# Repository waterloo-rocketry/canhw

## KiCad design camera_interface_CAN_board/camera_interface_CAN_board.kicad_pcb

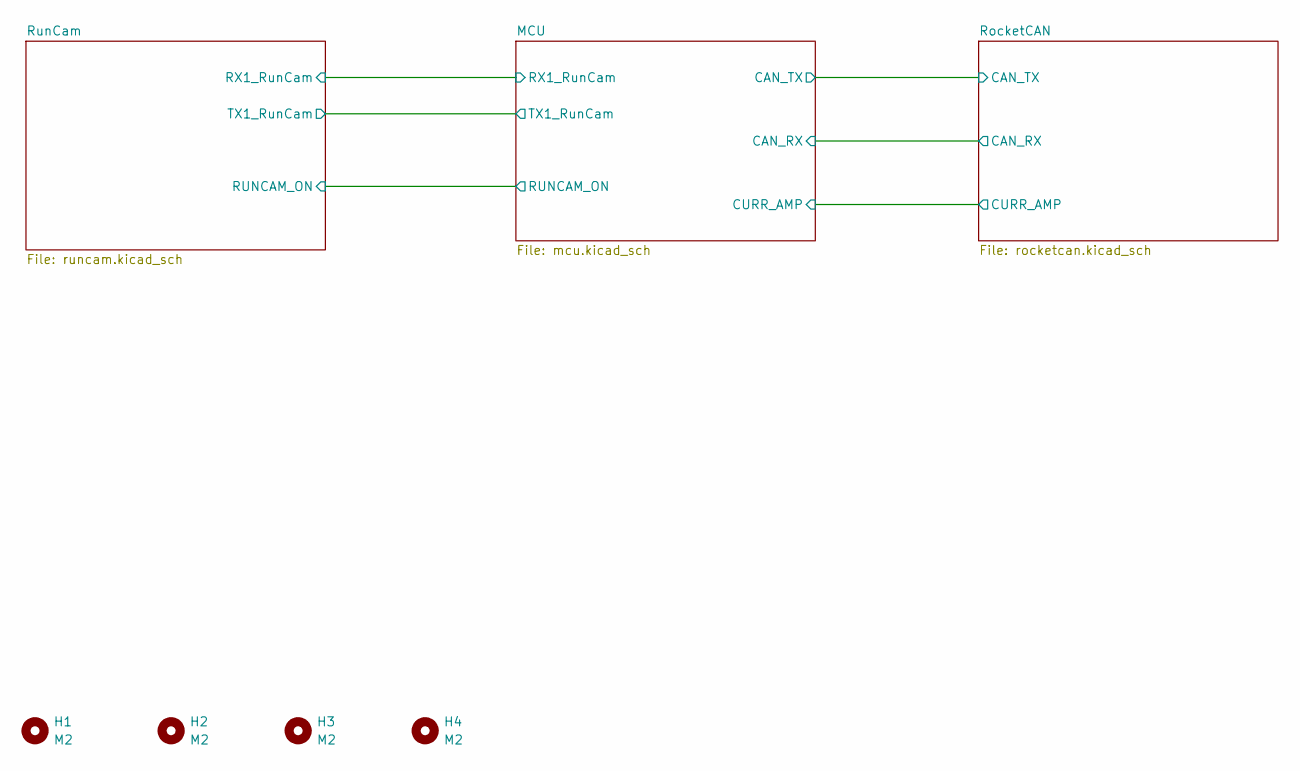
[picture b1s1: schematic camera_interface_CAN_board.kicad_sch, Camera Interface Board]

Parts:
H1, H2, H3, H4: M2; MountingHole_2.2mm_M2

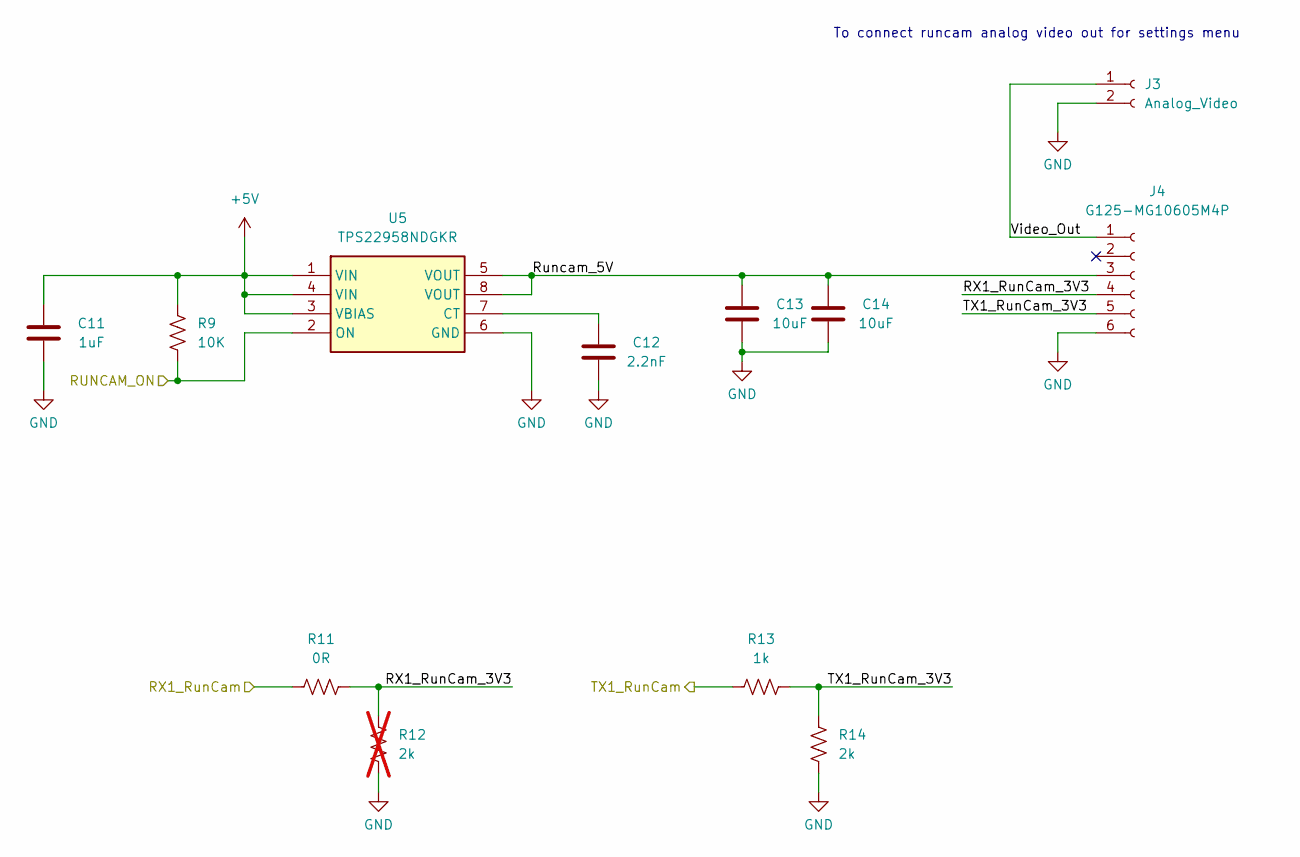
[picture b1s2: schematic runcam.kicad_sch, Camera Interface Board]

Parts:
C11: 1uF; C_0603_1608Metric_Pad1.08x0.95mm_HandSolder
C12: 2.2nF; C_0603_1608Metric_Pad1.08x0.95mm_HandSolder
C13, C14: 10uF; C_0805_2012Metric_Pad1.18x1.45mm_HandSolder
J3: Analog_Video; PinSocket_1x02_P1.27mm_Vertical
J4: G125-MG10605M4P; connector_Harwin_G125–MG10605M4P
R9: 10K; R_0603_1608Metric_Pad0.98x0.95mm_HandSolder
R11: 0R; R_0603_1608Metric_Pad0.98x0.95mm_HandSolder
R12: 2k; R_0603_1608Metric_Pad0.98x0.95mm_HandSolder; not fitted
R13: 1k; R_0603_1608Metric_Pad0.98x0.95mm_HandSolder
R14: 2k; R_0603_1608Metric_Pad0.98x0.95mm_HandSolder
U5: TPS22958NDGKR; SOP65P490X110-8N; Manufacturer_Part_Number TPS22958NDGKR

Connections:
+5V: C11.2, R9.1, U5.1 (VIN), U5.3 (VBIAS), U5.4 (VIN); also elsewhere on the board
/MCU/RUNCAM_ON: R9.2, U5.2 (ON); also elsewhere on the board
/MCU/RX1_RunCam: R11.1; also elsewhere on the board
/MCU/TX1_RunCam: R13.1; also elsewhere on the board
/RunCam/RX1_RunCam_3V3: J4.4, R11.2, R12.2
/RunCam/Runcam_5V: C13.2, C14.2, J4.3, U5.5 (VOUT), U5.8 (VOUT)
/RunCam/TX1_RunCam_3V3: J4.5, R13.2, R14.2
/RunCam/Video_Out: J3.1, J4.1
GND: C11.1, C12.1, C13.1, C14.1, J3.2, J4.6, R12.1, R14.1, U5.6 (GND); also elsewhere on the board
unnamed: C12.2, U5.7 (CT)

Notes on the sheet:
To connect runcam analog video out for settings menu

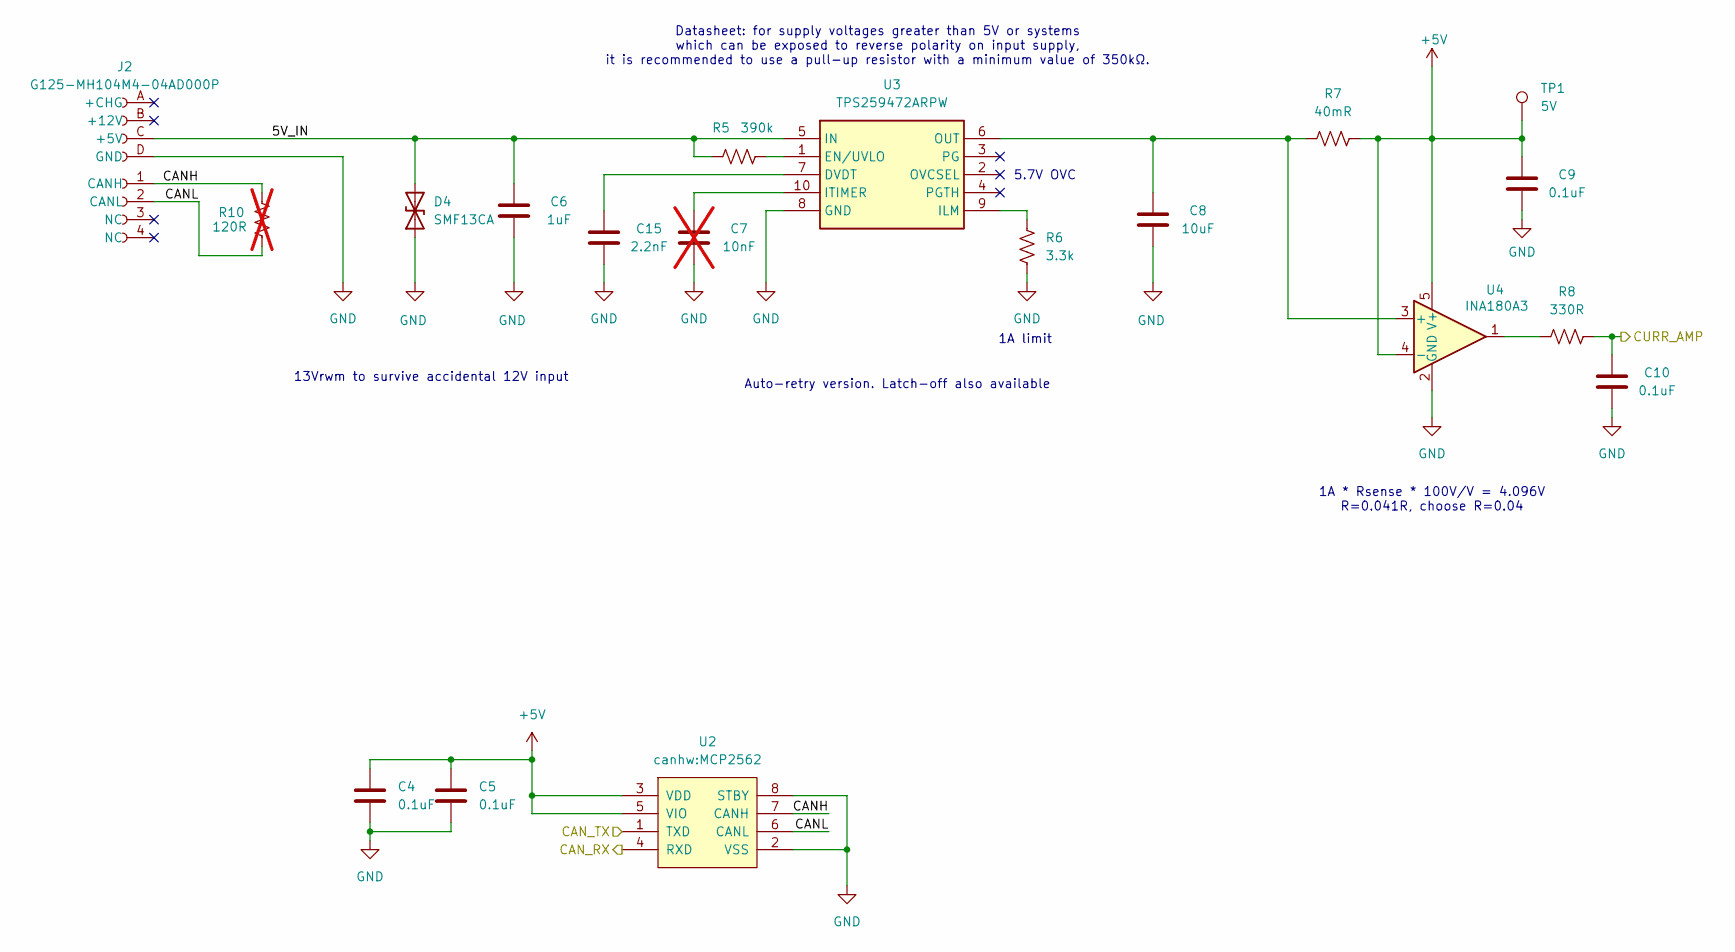
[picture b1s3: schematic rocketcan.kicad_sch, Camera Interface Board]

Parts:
C4, C5, C9, C10: 0.1uF; C_0603_1608Metric_Pad1.08x0.95mm_HandSolder
C6: 1uF; C_0603_1608Metric_Pad1.08x0.95mm_HandSolder
C7: 10nF; C_0603_1608Metric_Pad1.08x0.95mm_HandSolder; not fitted
C8: 10uF; C_0805_2012Metric_Pad1.18x1.45mm_HandSolder
C15: 2.2nF; C_0603_1608Metric_Pad1.08x0.95mm_HandSolder
D4: SMF13CA; D_SMF
J2: G125-MH104M4-04AD000P; connector_Harwin_G125-MH104M4-04AD000P
R5: 390k; R_0603_1608Metric_Pad0.98x0.95mm_HandSolder
R6: 3.3k; R_0603_1608Metric_Pad0.98x0.95mm_HandSolder
R7: 40mR; R_0805_2012Metric_Pad1.20x1.40mm_HandSolder
R8: 330R; R_0603_1608Metric_Pad0.98x0.95mm_HandSolder
R10: 120R; R_0603_1608Metric_Pad0.98x0.95mm_HandSolder; not fitted
TP1: 5V; TestPoint_Pad_D1.0mm
U2: canhw:MCP2562; SOIC-8_3.9x4.9mm_P1.27mm
U3: TPS259472ARPW; TPS25947xx
U4: INA180A3; SOT-23-5_HandSoldering

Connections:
+5V: C4.1, C5.1, C9.2, R7.1, TP1.1 (1_1), U2.3 (VDD), U2.5 (VIO), U4.4 (-), U4.5 (V+); also elsewhere on the board
/MCU/CAN_RX: U2.4 (RXD); also elsewhere on the board
/MCU/CAN_TX: U2.1 (TXD); also elsewhere on the board
/MCU/CURR_AMP: C10.2, R8.1; also elsewhere on the board
/RocketCAN/5V_IN: C6.2, D4.2 (A2), J2.C (+5V), R5.1, U3.5 (IN)
/RocketCAN/CANH: J2.1 (CANH), R10.2, U2.7 (CANH)
/RocketCAN/CANL: J2.2 (CANL), R10.1, U2.6 (CANL)
GND: C4.2, C5.2, C6.1, C7.1, C8.1, C9.1, C10.1, C15.1, D4.1 (A1), J2.D (GND), R6.2, U2.2 (VSS), U2.8 (STBY), U3.8 (GND), U4.2 (GND); also elsewhere on the board
unnamed: R8.2, U4.1
unnamed: C15.2, U3.7 (DVDT)
unnamed: R5.2, U3.1 (EN/UVLO)
unnamed: R6.1, U3.9 (ILM)
unnamed: C7.2, U3.10 (ITIMER)
unnamed: C8.2, R7.2, U3.6 (OUT), U4.3 (+)

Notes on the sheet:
13Vrwm to survive accidental 12V input
Auto-retry version. Latch-off also available
5.7V OVC
Datasheet: for supply voltages greater than 5V or systems which can be exposed to reverse polarity on input supply, it is recommended to use a pull-up resistor with a minimum value of 350kΩ.
1A limit
1A * Rsense * 100V/V = 4.096V R=0.041R, choose R=0.04

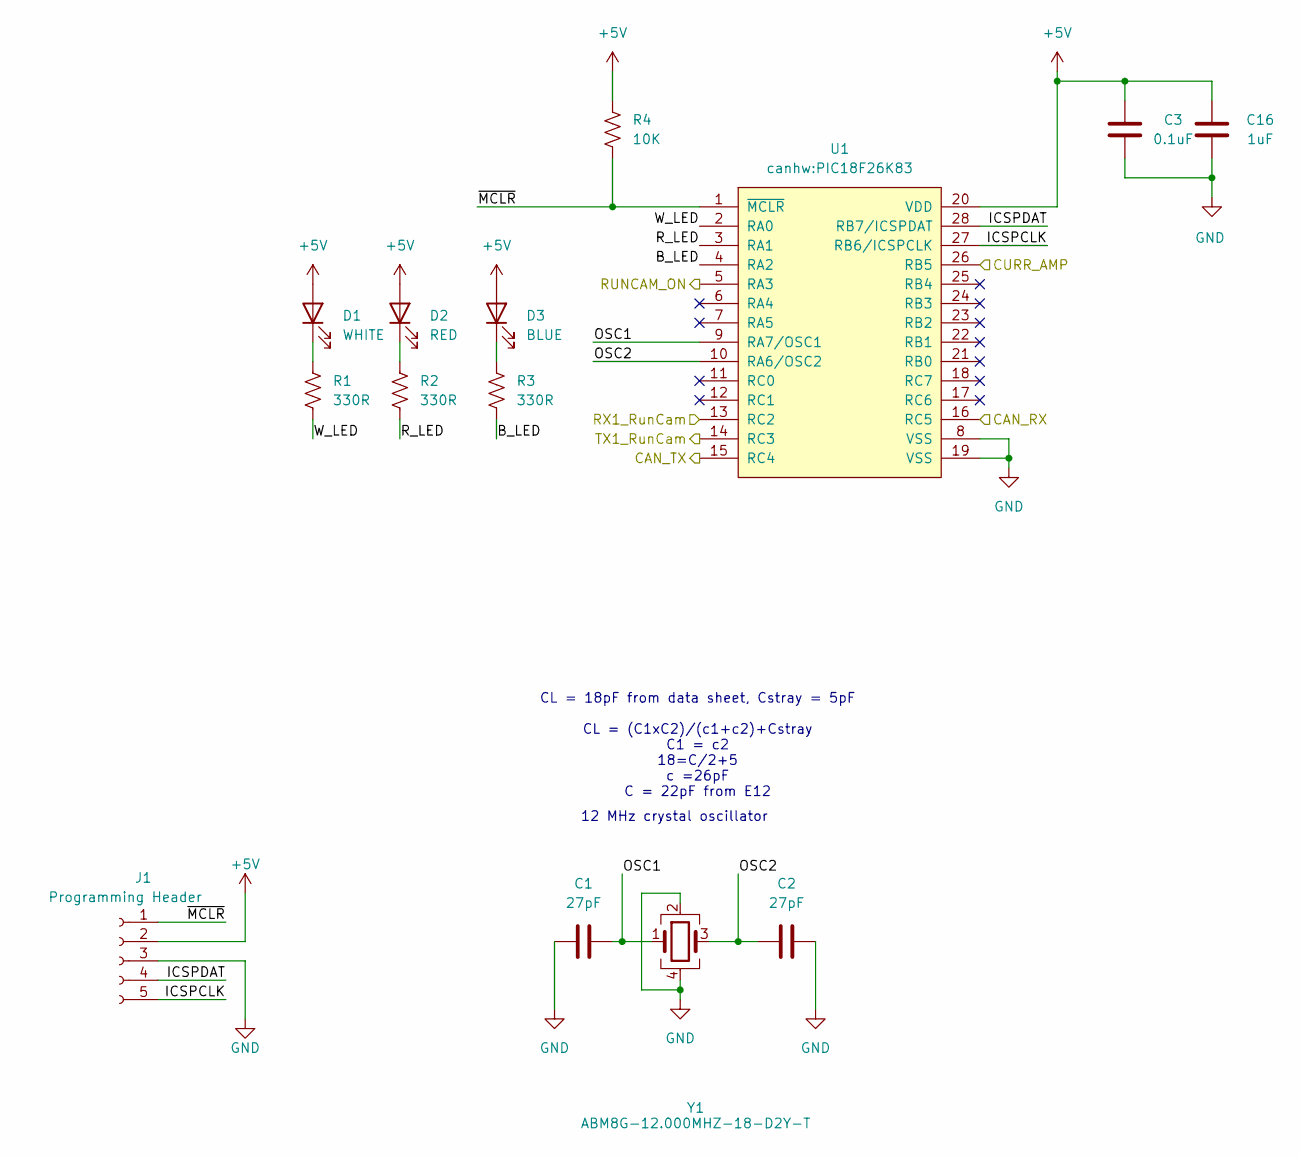
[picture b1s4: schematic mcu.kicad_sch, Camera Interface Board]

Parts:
C1, C2: 27pF; C_0603_1608Metric_Pad1.08x0.95mm_HandSolder
C3: 0.1uF; C_0603_1608Metric_Pad1.08x0.95mm_HandSolder
C16: 1uF; C_0603_1608Metric_Pad1.08x0.95mm_HandSolder
D1: WHITE; LED_1206_3216Metric
D2: RED; LED_1206_3216Metric
D3: BLUE; LED_1206_3216Metric
J1: Programming Header; PinSocket_5x2.54_SMD_90deg_952-3198-1-ND
R1, R2, R3: 330R; R_0603_1608Metric_Pad0.98x0.95mm_HandSolder
R4: 10K; R_0603_1608Metric_Pad0.98x0.95mm_HandSolder
U1: canhw:PIC18F26K83; SOIC-28W_7.5x18.7mm_P1.27mm
Y1: ABM8G-12.000MHZ-18-D2Y-T; Crystal_SMD_Abracon_ABM8G-4Pin_3.2x2.5mm

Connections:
+5V: C3.2, C16.2, D1.2 (A), D2.2 (A), D3.2 (A), J1.2, R4.1, U1.20 (VDD); also elsewhere on the board
/MCU/B_LED: R3.2, U1.4 (RA2)
/MCU/CAN_RX: U1.16 (RC5); also elsewhere on the board
/MCU/CAN_TX: U1.15 (RC4); also elsewhere on the board
/MCU/CURR_AMP: U1.26 (RB5); also elsewhere on the board
/MCU/ICSPCLK: J1.5, U1.27 (RB6/ICSPCLK)
/MCU/ICSPDAT: J1.4, U1.28 (RB7/ICSPDAT)
/MCU/OSC1: C1.1, U1.9 (RA7/OSC1), Y1.1
/MCU/OSC2: C2.2, U1.10 (RA6/OSC2), Y1.3
/MCU/RUNCAM_ON: U1.5 (RA3); also elsewhere on the board
/MCU/RX1_RunCam: U1.13 (RC2); also elsewhere on the board
/MCU/R_LED: R2.2, U1.3 (RA1)
/MCU/TX1_RunCam: U1.14 (RC3); also elsewhere on the board
/MCU/W_LED: R1.2, U1.2 (RA0)
/MCU/~MCLR: J1.1, R4.2, U1.1 (~MCLR)
GND: C1.2, C2.1, C3.1, C16.1, J1.3, U1.8 (VSS), U1.19 (VSS), Y1.2, Y1.4; also elsewhere on the board
unnamed: D1.1 (K), R1.1
unnamed: D2.1 (K), R2.1
unnamed: D3.1 (K), R3.1

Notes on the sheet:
12 MHz crystal oscillator
CL = 18pF from data sheet, Cstray = 5pF CL = (C1xC2)/(c1+c2)+Cstray C1 = c2 18=C​/2+5 c =26pF C = 22pF from E12​

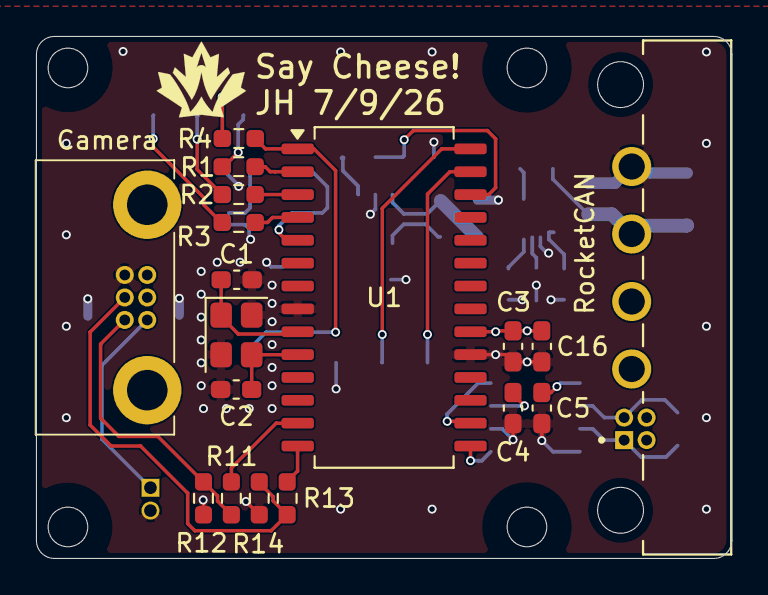
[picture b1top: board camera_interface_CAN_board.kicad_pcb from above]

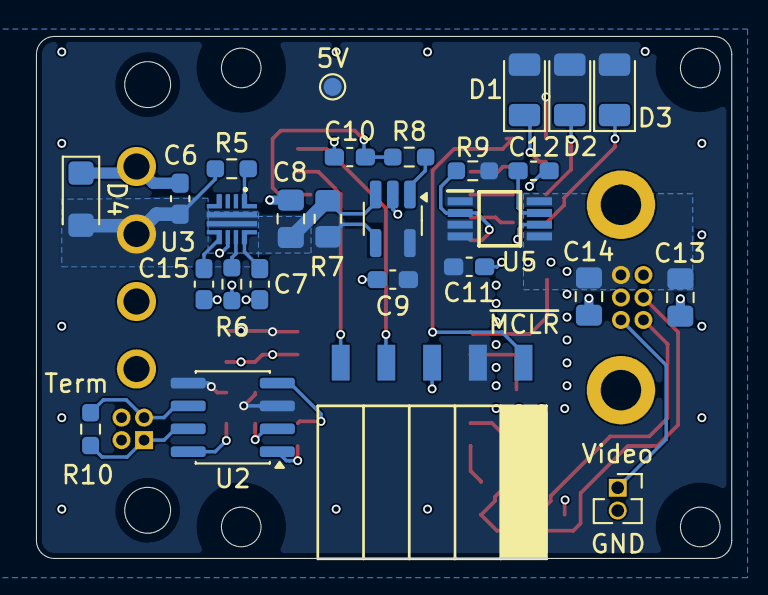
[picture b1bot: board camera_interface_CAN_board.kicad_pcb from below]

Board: 4 copper layers, 38.6 x 29.0 mm, 49 parts (27 on the bottom side), 33 nets.

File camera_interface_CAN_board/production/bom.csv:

Designator,Footprint,Quantity,Value,LCSC Part #
"C1, C2",0603,2,27pF,
"C10, C3, C4, C5, C9",0603,5,0.1uF,
"C11, C16, C6",0603,3,1uF,
"C12, C15",0603,2,2.2nF,
"C13, C14, C8",0805,3,10uF,
C7,0603,1,10nF,
D1,1206,1,WHITE,
D2,1206,1,RED,
D3,1206,1,BLUE,
D4,D_SMF,1,SMF13CA,
J1,PinSocket_5x2.54_SMD_90deg_952-3198-1-ND,1,Programming Header,
J2,connector_Harwin_G125-MH104M4-04AD000P,1,G125-MH104M4-04AD000P,
J3,PinSocket_1x02_P1.27mm_Vertical,1,Analog_Video,
J4,connector_Harwin_G125–MG10605M4P,1,G125-MG10605M4P,
"R1, R2, R3, R8",0603,4,330R,
R10,0603,1,120R,
R11,0603,1,0R,
"R12, R14",0603,2,2k,
R13,0603,1,1k,
"R4, R9",0603,2,10K,
R5,0603,1,390k,
R6,0603,1,3.3k,
R7,0805,1,40mR,
TP1,TestPoint_Pad_D1.0mm,1,5V,
U1,SOIC-28W_7.5x18.7mm_P1.27mm,1,canhw:PIC18F26K83,
U2,SOIC-8_3.9x4.9mm_P1.27mm,1,canhw:MCP2562,
U3,TPS25947xx,1,TPS259472ARPW,
U4,SOT-23-5_HandSoldering,1,INA180A3,
U5,SOP65P490X110-8N,1,TPS22958NDGKR,
Y1,Crystal_SMD_Abracon_ABM8G-4Pin_3.2x2.5mm,1,ABM8G-12.000MHZ-18-D2Y-T,

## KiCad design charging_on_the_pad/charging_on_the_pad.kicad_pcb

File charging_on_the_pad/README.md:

# Charging On the Pad 
A charger board on the CAN bus that includes the battery, charging port connection, and additional power connections to live telemetry transmitter.
Clickup: https://app.clickup.com/8608989/v/li/176275976
Drive: https://drive.google.com/drive/folders/1WU_OsI1vf2b53sMAvz4AfjsN1jmYpsuN?usp=sharing

The system must provide CAN communication to the rocket from the ground side as long as the rocket is on the pad
The system should report the charge status, battery voltage, and current to CAN bus
The system should be able to turn off or on the CAN bus power. LTT should be kept 
The connector must be strong enough to stay in by itself, but weak enough to be pulled off by the rocket without affecting the launch

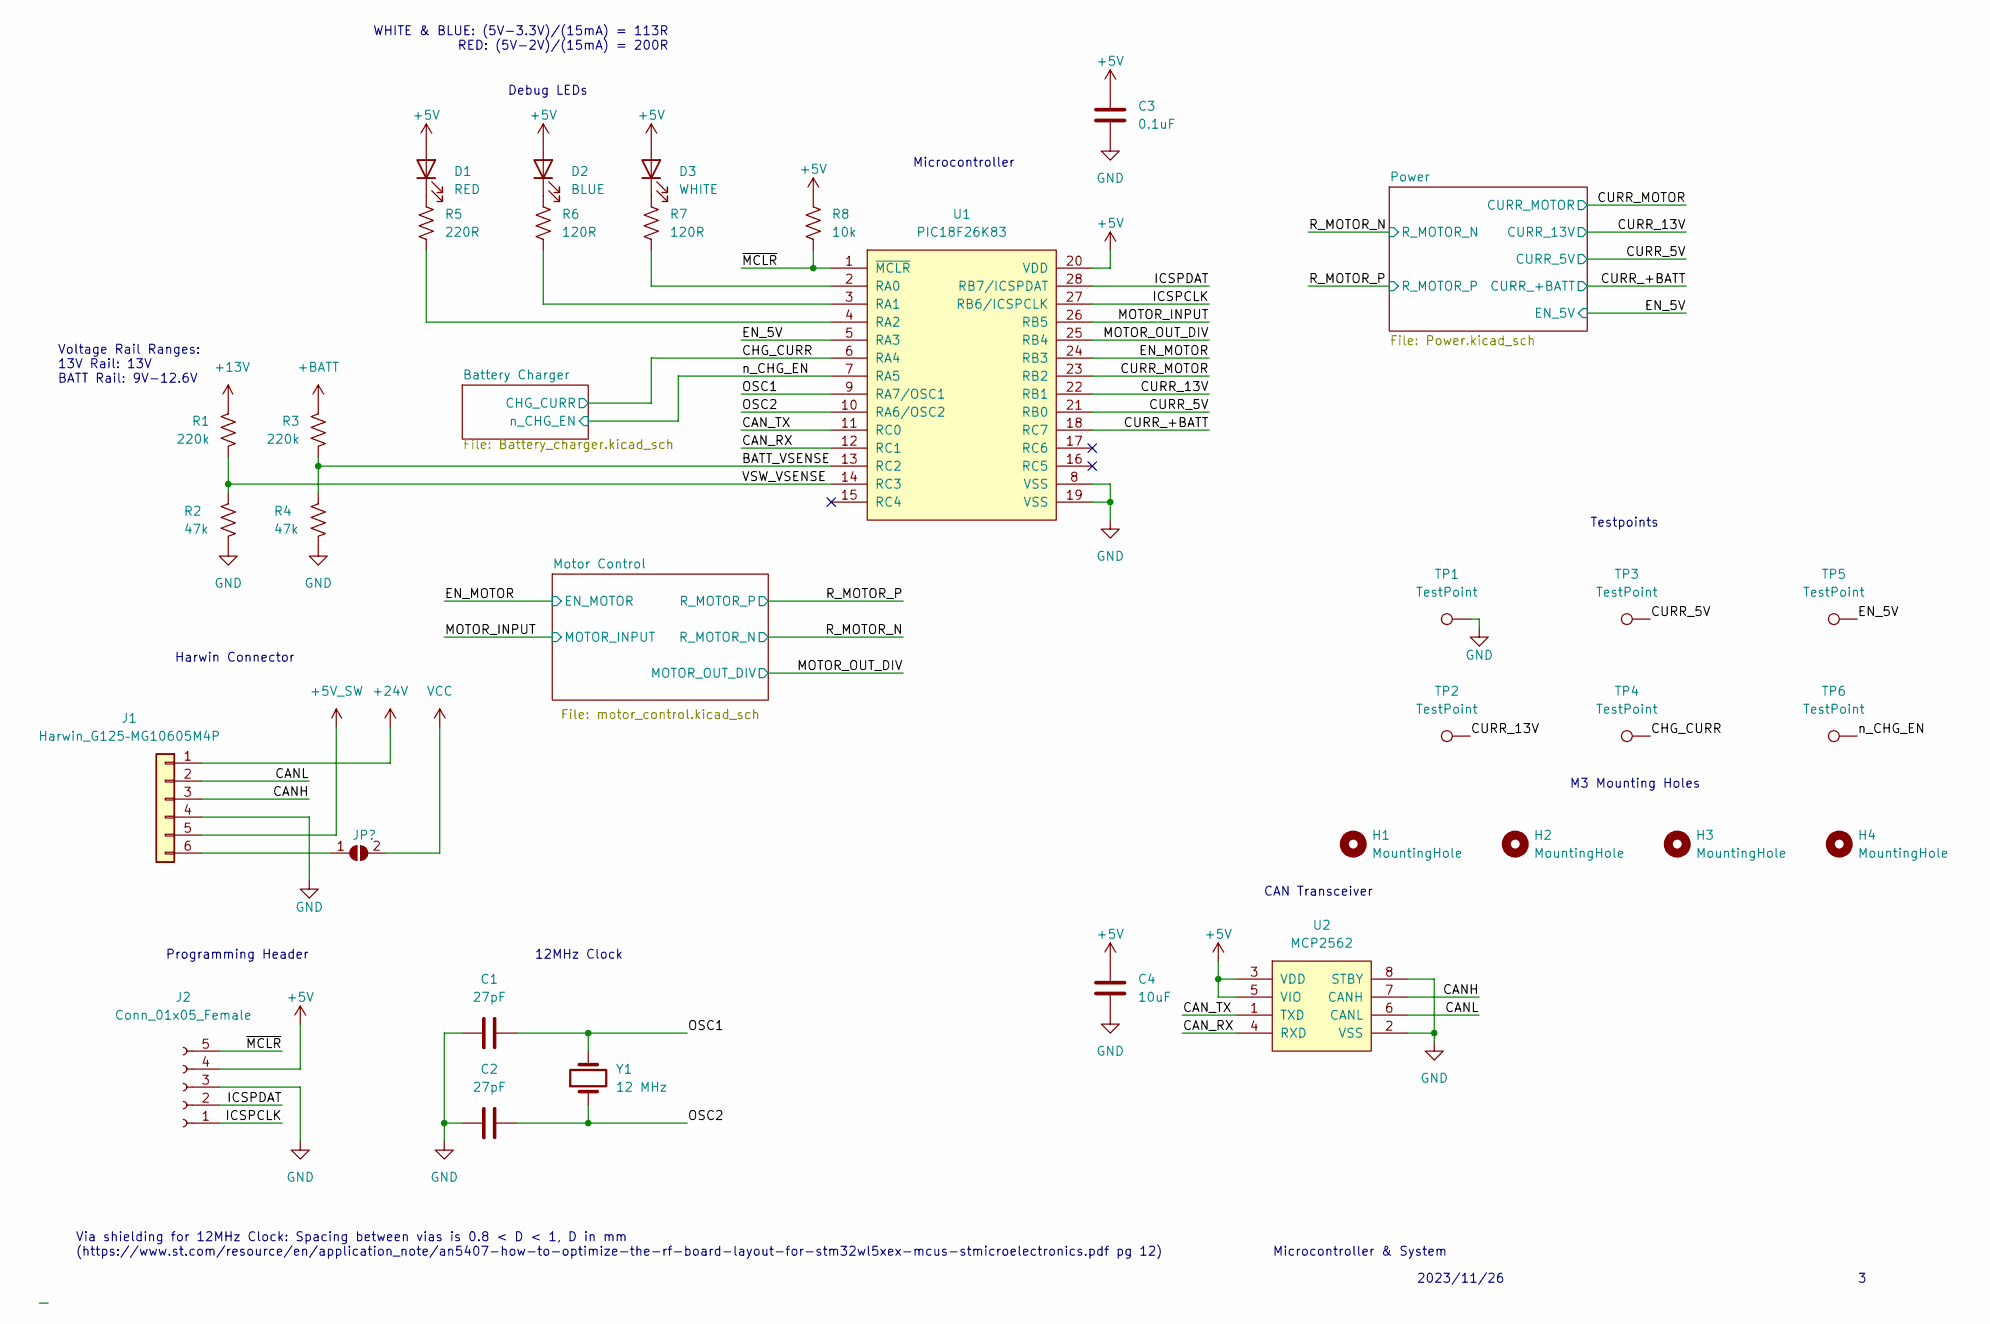
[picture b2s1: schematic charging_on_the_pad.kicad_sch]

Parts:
C1, C2: 27pF; C_0805_2012Metric_Pad1.18x1.45mm_HandSolder
C3: 0.1uF; C_0805_2012Metric_Pad1.18x1.45mm_HandSolder
C4: 10uF; C_0805_2012Metric_Pad1.18x1.45mm_HandSolder
D1: RED; LED_1206_3216Metric_Pad1.42x1.75mm_HandSolder
D2: BLUE; LED_1206_3216Metric_Pad1.42x1.75mm_HandSolder
D3: WHITE; LED_1206_3216Metric_Pad1.42x1.75mm_HandSolder
H1, H2, H3, H4: MountingHole; MountingHole_3.2mm_M3_Pad
J1: Harwin_G125–MG10605M4P; connector_Harwin_G125–MG10605M4P
J2: Conn_01x05_Female; PinHeader_5x2.54_SMD_90deg_952-3198-1-ND
JP1: SolderJumper_2_Open; SolderJumper-2_P1.3mm_Open_RoundedPad1.0x1.5mm
R1, R3: 220k; R_0805_2012Metric_Pad1.20x1.40mm_HandSolder
R2, R4: 47k; R_0805_2012Metric_Pad1.20x1.40mm_HandSolder
R5: 220R; R_0805_2012Metric_Pad1.20x1.40mm_HandSolder
R6, R7: 120R; R_0805_2012Metric_Pad1.20x1.40mm_HandSolder
R8: 10k; R_0805_2012Metric_Pad1.20x1.40mm_HandSolder
TP1, TP2, TP3, TP4, TP5, TP6: TestPoint; TestPoint_Pad_1.0x1.0mm
U1: PIC18F26K83; SOIC-28W_7.5x18.7mm_P1.27mm
U2: MCP2562; SOIC-8_3.9x4.9mm_P1.27mm
Y1: 12 MHz; Crystal_HC49-4H_Vertical

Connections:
+5V: C3.1, C4.1, D1.2 (A), D2.2 (A), D3.2 (A), J2.4, R8.1, U1.20 (VDD), U2.3 (VDD), U2.5 (VIO); also elsewhere on the board
+5V_PWR: J1.5; also elsewhere on the board
+13V: R1.1; also elsewhere on the board
+24V: J1.1; also elsewhere on the board
+BATT: R3.1; also elsewhere on the board
/BATT_VSENSE: R3.2, R4.1, U1.13 (RC2)
/CANH: J1.3, U2.7 (CANH)
/CANL: J1.2, U2.6 (CANL)
/CAN_RX: U1.12 (RC1), U2.4 (RXD)
/CAN_TX: U1.11 (RC0), U2.1 (TXD)
/CHG_CURR: TP4.1, U1.6 (RA4); also elsewhere on the board
/CURR_5V: TP3.1, U1.21 (RB0); also elsewhere on the board
/CURR_13V: TP2.1, U1.22 (RB1); also elsewhere on the board
/CURR_+BATT: U1.18 (RC7); also elsewhere on the board
/CURR_MOTOR: U1.23 (RB2); also elsewhere on the board
/EN_5V: TP5.1, U1.5 (RA3); also elsewhere on the board
/EN_MOTOR: U1.24 (RB3); also elsewhere on the board
/ICSPCLK: J2.1, U1.27 (RB6/ICSPCLK)
/ICSPDAT: J2.2, U1.28 (RB7/ICSPDAT)
/MOTOR_INPUT: U1.26 (RB5); also elsewhere on the board
/MOTOR_OUT_DIV: U1.25 (RB4); also elsewhere on the board
/OSC1: C1.1, U1.9 (RA7/OSC1), Y1.2
/OSC2: C2.1, U1.10 (RA6/OSC2), Y1.1
/VSW_VSENSE: R1.2, R2.1, U1.14 (RC3)
/n_CHG_EN: TP6.1, U1.7 (RA5); also elsewhere on the board
/~MCLR: J2.5, R8.2, U1.1 (~MCLR)
GND: C1.2, C2.2, C3.2, C4.2, J1.4, J2.3, R2.2, R4.2, TP1.1, U1.8 (VSS), U1.19 (VSS), U2.2 (VSS), U2.8 (STBY); also elsewhere on the board
unnamed: D1.1 (K), R5.1
unnamed: D2.1 (K), R6.1
unnamed: D3.1 (K), R7.1
unnamed 45: J1.6, JP1.1 (A); also elsewhere on the board
unnamed: R7.2, U1.2 (RA0)
unnamed: R6.2, U1.3 (RA1)
unnamed: R5.2, U1.4 (RA2)

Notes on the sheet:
2023/11/26
CAN Transceiver
Programming Header
Debug LEDs
Microcontroller & System
12MHz Clock
Harwin Connector
Testpoints
WHITE & BLUE: (5V-3.3V)/(15mA) = 113R RED: (5V-2V)/(15mA) = 200R
Voltage Rail Ranges: 13V Rail: 13V BATT Rail: 9V-12.6V
M3 Mounting Holes
Microcontroller
Via shielding for 12MHz Clock: Spacing between vias is 0.8 < D < 1, D in mm (https://www.st.com/resource/en/application_note/an5407-how-to-optimize-the-rf-board-layout-for-stm32wl5xex-mcus-stmicroelectronics.pdf pg 12)

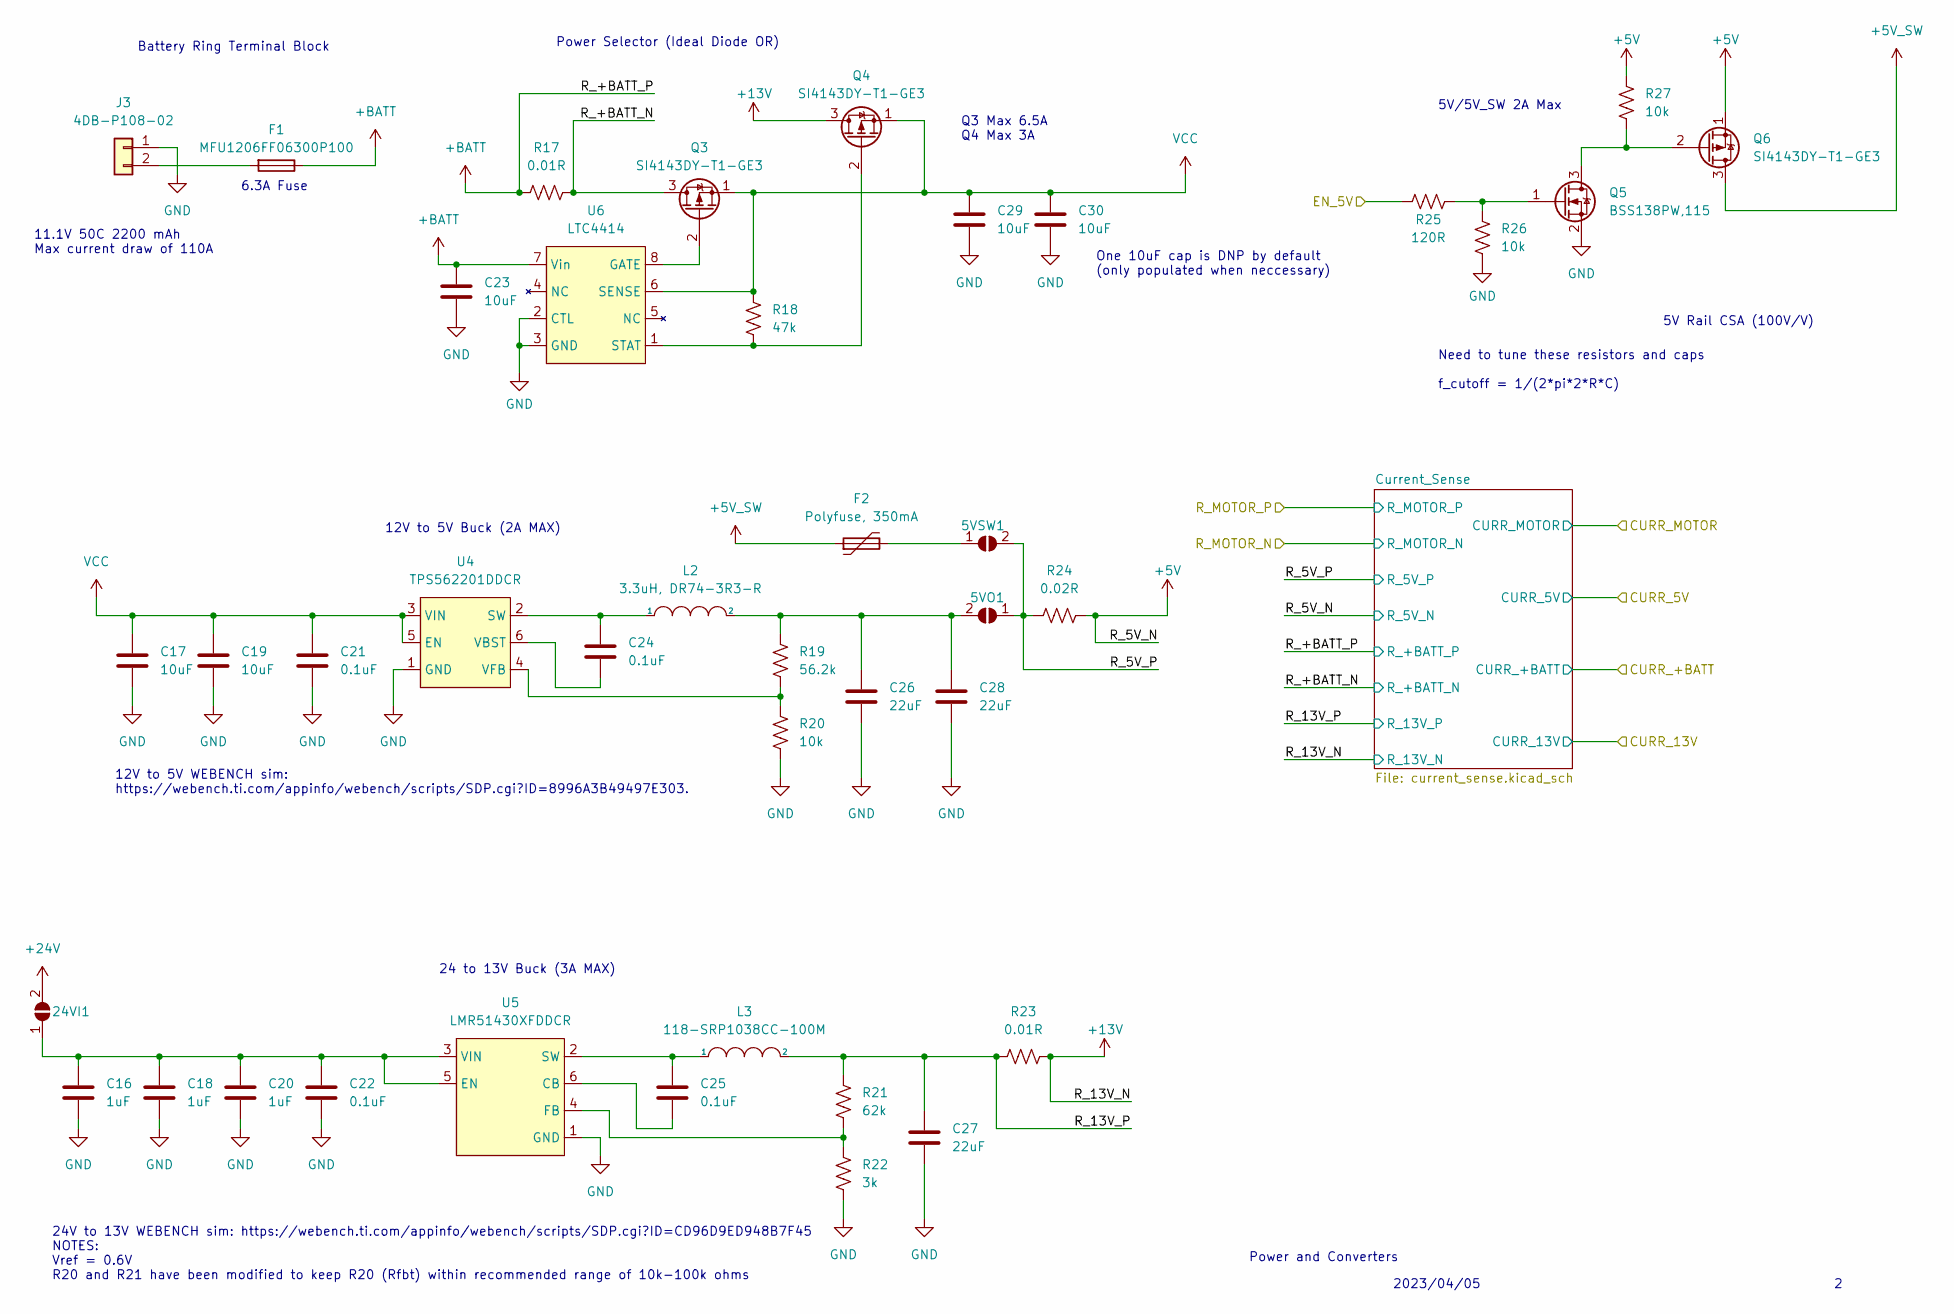
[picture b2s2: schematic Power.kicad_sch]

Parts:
5VO1, 5VSW1, 24VI1: SolderJumper_2_Open; SolderJumper-2_P1.3mm_Open_RoundedPad1.0x1.5mm
C16, C18, C20: 1uF; C_0805_2012Metric_Pad1.18x1.45mm_HandSolder
C17, C19, C23, C29, C30: 10uF; C_0805_2012Metric_Pad1.18x1.45mm_HandSolder
C21, C22, C24, C25: 0.1uF; C_0805_2012Metric_Pad1.18x1.45mm_HandSolder
C26, C28: 22uF; C_0805_2012Metric_Pad1.18x1.45mm_HandSolder
C27: 22uF; C_1210_3225Metric_Pad1.33x2.70mm_HandSolder
F1: MFU1206FF06300P100; Fuse_1206_3216Metric_Pad1.42x1.75mm_HandSolder
F2: Polyfuse, 350mA; Fuse_1206_3216Metric_Pad1.42x1.75mm_HandSolder
J3: 4DB-P108-02; TE_2-1437667-4
L2: 3.3uH, DR74-3R3-R; DR74-3R3-R
L3: 118-SRP1038CC-100M; L_Bourns_SRP1038C_10.0x10.0mm
Q3, Q4, Q6: SI4143DY-T1-GE3
Q5: BSS138PW,115; SOT-323_SC-70_Handsoldering
R17, R23: 0.01R; C_1206_3216Metric_Pad1.33x1.80mm_HandSolder
R18: 47k; R_0805_2012Metric_Pad1.20x1.40mm_HandSolder
R19: 56.2k; R_0805_2012Metric_Pad1.20x1.40mm_HandSolder
R20, R26, R27: 10k; R_0805_2012Metric_Pad1.20x1.40mm_HandSolder
R21: 62k; R_0805_2012Metric_Pad1.20x1.40mm_HandSolder
R22: 3k; R_0805_2012Metric_Pad1.20x1.40mm_HandSolder
R24: 0.02R; R_1206_3216Metric_Pad1.30x1.75mm_HandSolder
R25: 120R; R_0805_2012Metric_Pad1.20x1.40mm_HandSolder
U4: TPS562201DDCR; SOT-23-6_Handsoldering
U5: LMR51430XFDDCR; SOT-23-6_Handsoldering
U6: LTC4414

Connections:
+5V: Q6.1 (S), R24.1, R27.1; also elsewhere on the board
+5V_PWR: F2.1, Q6.3 (D); also elsewhere on the board
+13V: Q4.3 (D), R23.2; also elsewhere on the board
+24V: 24VI1.2 (B); also elsewhere on the board
+BATT: C23.1, F1.1, R17.2, U6.7 (Vin); also elsewhere on the board
/EN_5V: R25.1; also elsewhere on the board
/Power/R_5V_P: 5VO1.1 (A), 5VSW1.2 (B), R24.2; also elsewhere on the board
/Power/R_13V_P: C27.1, L3.2, R21.1, R23.1; also elsewhere on the board
/Power/R_+BATT_N: Q3.3 (D), R17.1; also elsewhere on the board
GND: C16.2, C17.2, C18.2, C19.2, C20.2, C21.2, C22.2, C23.2, C26.2, C27.2, C28.2, C29.2, C30.2, J3.1, Q5.2 (S), R20.2, R22.2, R26.2, U4.1 (GND), U5.1 (GND), U6.2 (CTL), U6.3 (GND); also elsewhere on the board
unnamed: 5VO1.2 (B), C26.1, C28.1, L2.2, R19.1
unnamed: 5VSW1.1 (A), F2.2
unnamed: 24VI1.1 (A), C16.1, C18.1, C20.1, C22.1, U5.3 (VIN), U5.5 (EN)
unnamed: F1.2, J3.2
unnamed: Q3.2 (G), U6.8 (GATE)
unnamed: Q4.2 (G), R18.2, U6.1 (STAT)
unnamed: Q5.3 (D), Q6.2 (G), R27.2
unnamed: Q5.1 (G), R25.2, R26.1
unnamed: C24.1, L2.1, U4.2 (SW)
unnamed: C24.2, U4.6 (VBST)
unnamed: R19.2, R20.1, U4.4 (VFB)
unnamed: C25.2, U5.6 (CB)
unnamed: R21.2, R22.1, U5.4 (FB)
unnamed: C25.1, L3.1, U5.2 (SW)
VCC: C17.1, C19.1, C21.1, C29.1, C30.1, Q3.1 (S), Q4.1 (S), R18.1, U4.3 (VIN), U4.5 (EN), U6.6 (SENSE); also elsewhere on the board

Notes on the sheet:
12V to 5V WEBENCH sim: https://webench.ti.com/appinfo/webench/scripts/SDP.cgi?ID=8996A3B49497E303.
Q3 Max 6.5A Q4 Max 3A
Power Selector (Ideal Diode OR)
Need to tune these resistors and caps f_cutoff = 1/(2*pi*2*R*C)
5V/5V_SW 2A Max
24 to 13V Buck (3A MAX)
Battery Ring Terminal Block
2023/04/05
6.3A Fuse
24V to 13V WEBENCH sim: https://webench.ti.com/appinfo/webench/scripts/SDP.cgi?ID=CD96D9ED948B7F45 NOTES: Vref = 0.6V R20 and R21 have been modified to keep R20 (Rfbt) within recommended range of 10k-100k ohms
One 10uF cap is DNP by default (only populated when neccessary)
5V Rail CSA (100V/V)
Power and Converters
12V to 5V Buck (2A MAX)
11.1V 50C 2200 mAh Max current draw of 110A

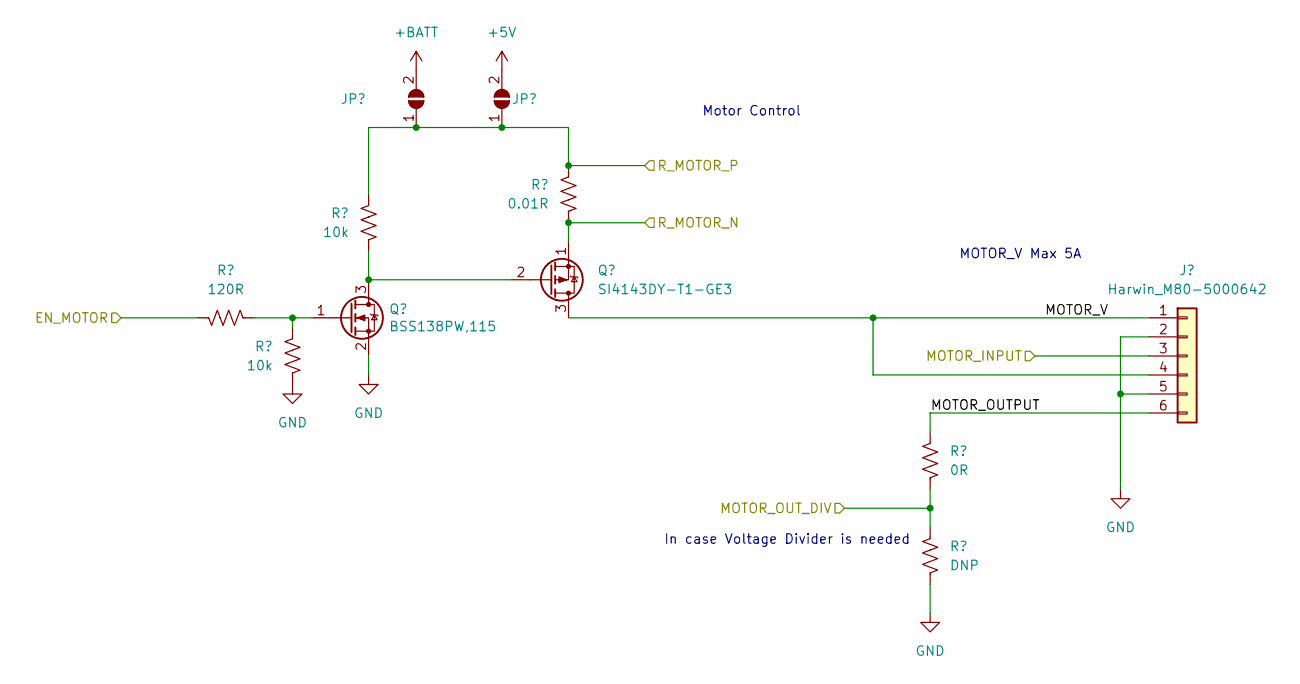
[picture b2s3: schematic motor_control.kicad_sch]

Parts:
5V2M1: SolderJumper_2_Open; SolderJumper-2_P1.3mm_Open_RoundedPad1.0x1.5mm
BATT2M1: SolderJumper_2_Open; SolderJumper-2_P1.3mm_Open_RoundedPad1.0x1.5mm
J4: Harwin_M80-5000642; connector_Harwin_M80-5000642
Q7: BSS138PW,115; SOT-23_Handsoldering
Q8: SI4143DY-T1-GE3
R36: 120R; R_0805_2012Metric_Pad1.20x1.40mm_HandSolder
R37, R38: 10k; R_0805_2012Metric_Pad1.20x1.40mm_HandSolder
R39: 0.01R; R_0805_2012Metric_Pad1.20x1.40mm_HandSolder
R40: 0R; R_0805_2012Metric_Pad1.20x1.40mm_HandSolder
R41: DNP; R_0805_2012Metric_Pad1.20x1.40mm_HandSolder

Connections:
+5V: 5V2M1.2 (B); also elsewhere on the board
+BATT: BATT2M1.2 (B); also elsewhere on the board
/EN_MOTOR: R36.1; also elsewhere on the board
/MOTOR_INPUT: J4.3; also elsewhere on the board
/MOTOR_OUT_DIV: R40.2, R41.1; also elsewhere on the board
/Motor Control/MOTOR_OUTPUT: J4.6, R40.1
/Motor Control/MOTOR_V: J4.1, J4.4, Q8.3 (D)
/R_MOTOR_N: Q8.1 (S), R39.2; also elsewhere on the board
/R_MOTOR_P: 5V2M1.1 (A), BATT2M1.1 (A), R38.1, R39.1; also elsewhere on the board
GND: J4.2, J4.5, Q7.2 (S), R37.2, R41.2; also elsewhere on the board
unnamed: Q7.3 (D), Q8.2 (G), R38.2
unnamed: Q7.1 (G), R36.2, R37.1

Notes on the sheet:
Motor Control
MOTOR_V Max 5A
In case Voltage Divider is needed
